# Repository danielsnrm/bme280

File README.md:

# bme280
bme280 with esp8266

Including low power. Initially using ESP-201. Then I want to use ESP-07.

I will add Eagle files for PCB Design with ESP-07.

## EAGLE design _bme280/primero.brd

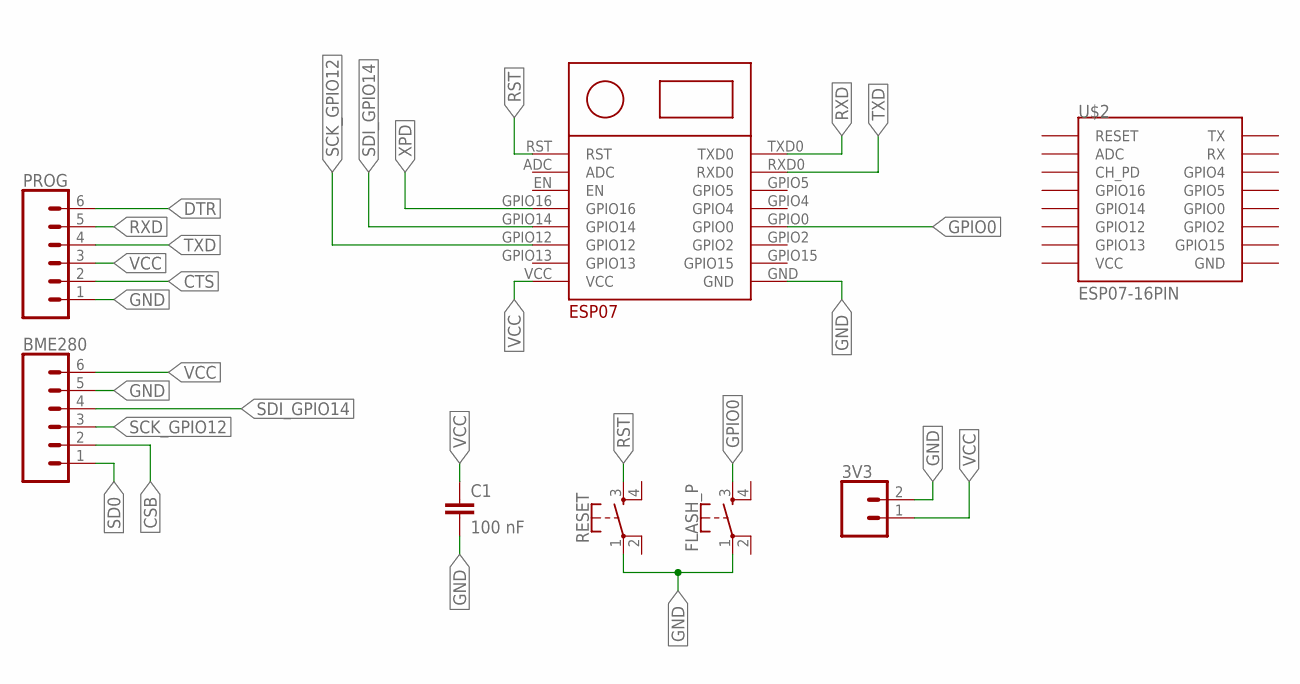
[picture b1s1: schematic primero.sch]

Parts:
3V3: CONN_02JST-PTH-2; JST-2-PTH
BME280: CONN_06SILK_FEMALE_PTH; 1X06
C1: 100 nF; C0805
FLASH_P: MOMENTARY-SWITCH-SPST-2-SMD-4.6X2.8MM; TACTILE_SWITCH_SMD_4.6X2.8MM
PROG: CONN_06SILK_FEMALE_PTH; 1X06
RESET: MOMENTARY-SWITCH-SPST-2-SMD-4.6X2.8MM; TACTILE_SWITCH_SMD_4.6X2.8MM
U$1: ESP-07ESP07; ESP-07_MM
U$2: ESP07-16PIN

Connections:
CSB: BME280.2
CTS: PROG.2
DTR: PROG.6
GND: 3V3.2, BME280.5, C1.2, FLASH_P.1, PROG.1, RESET.1, U$1.GND
GPIO0: FLASH_P.3, U$1.GPIO0
RST: RESET.3, U$1.RST
RXD: PROG.5, U$1.TXD0
SCK_GPIO12: BME280.3, U$1.GPIO12
SD0: BME280.1
SDI_GPIO14: BME280.4, U$1.GPIO14
TXD: PROG.4, U$1.RXD0
VCC: 3V3.1, BME280.6, C1.1, PROG.3, U$1.VCC
XPD: U$1.GPIO16

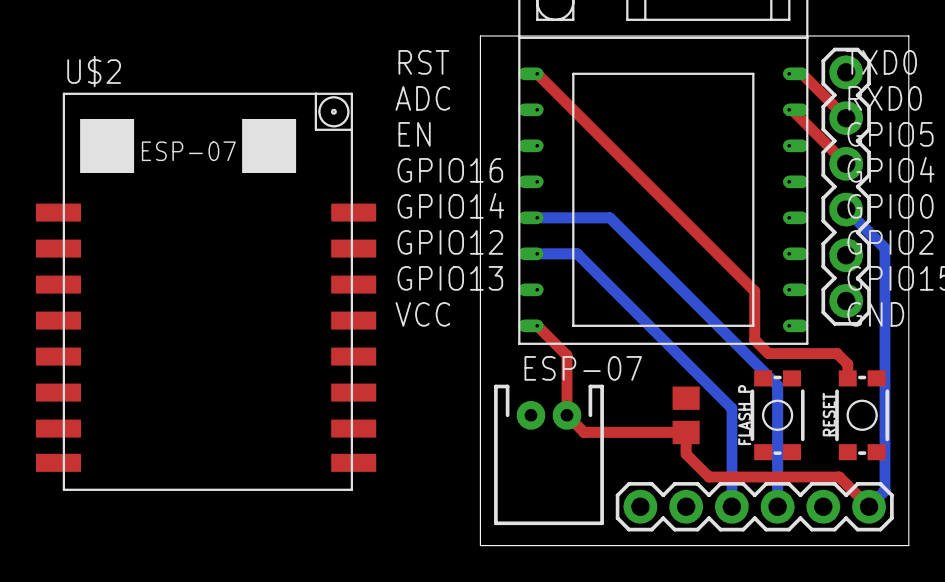
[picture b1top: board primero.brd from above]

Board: 2 copper layers, 23.8 x 28.3 mm, 8 parts (0 on the bottom side), 8 nets.

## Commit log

2019-05-05 Add files via upload
    First upload for BME280 with ESP-201
2019-05-05 Add files via upload
    Added a timing for avoid response from thingspeak. Must be handled properly but, for the time being it should be enough.
2019-05-05 Add files via upload
    Correct deleted characters.
2019-05-05 Add files via upload
    Versión operativa
2019-05-08 Create README.md
    First README version file.
2019-05-08 Create EAGLE
2019-05-08 Add files via upload
    Primera versión.
2019-05-08 Add files via upload
    Update.
2019-05-19 Add files via upload
    Este esquema hay que revisarlo, por si no está completo.
2019-05-19 versión preliminar de PCB
    -Añadido libreria:
    https://github.com/wvanvlaenderen/ESP8266-Eagle_Library
    - cambiados pulsadores a smd
    -distribución inicial de pcb

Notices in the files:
parts and their libraries:
SparkFun-Connectors: Licensing: Creative Commons ShareAlike 4.0 International - https://creativecommons.org/licenses/by-sa/4.0
